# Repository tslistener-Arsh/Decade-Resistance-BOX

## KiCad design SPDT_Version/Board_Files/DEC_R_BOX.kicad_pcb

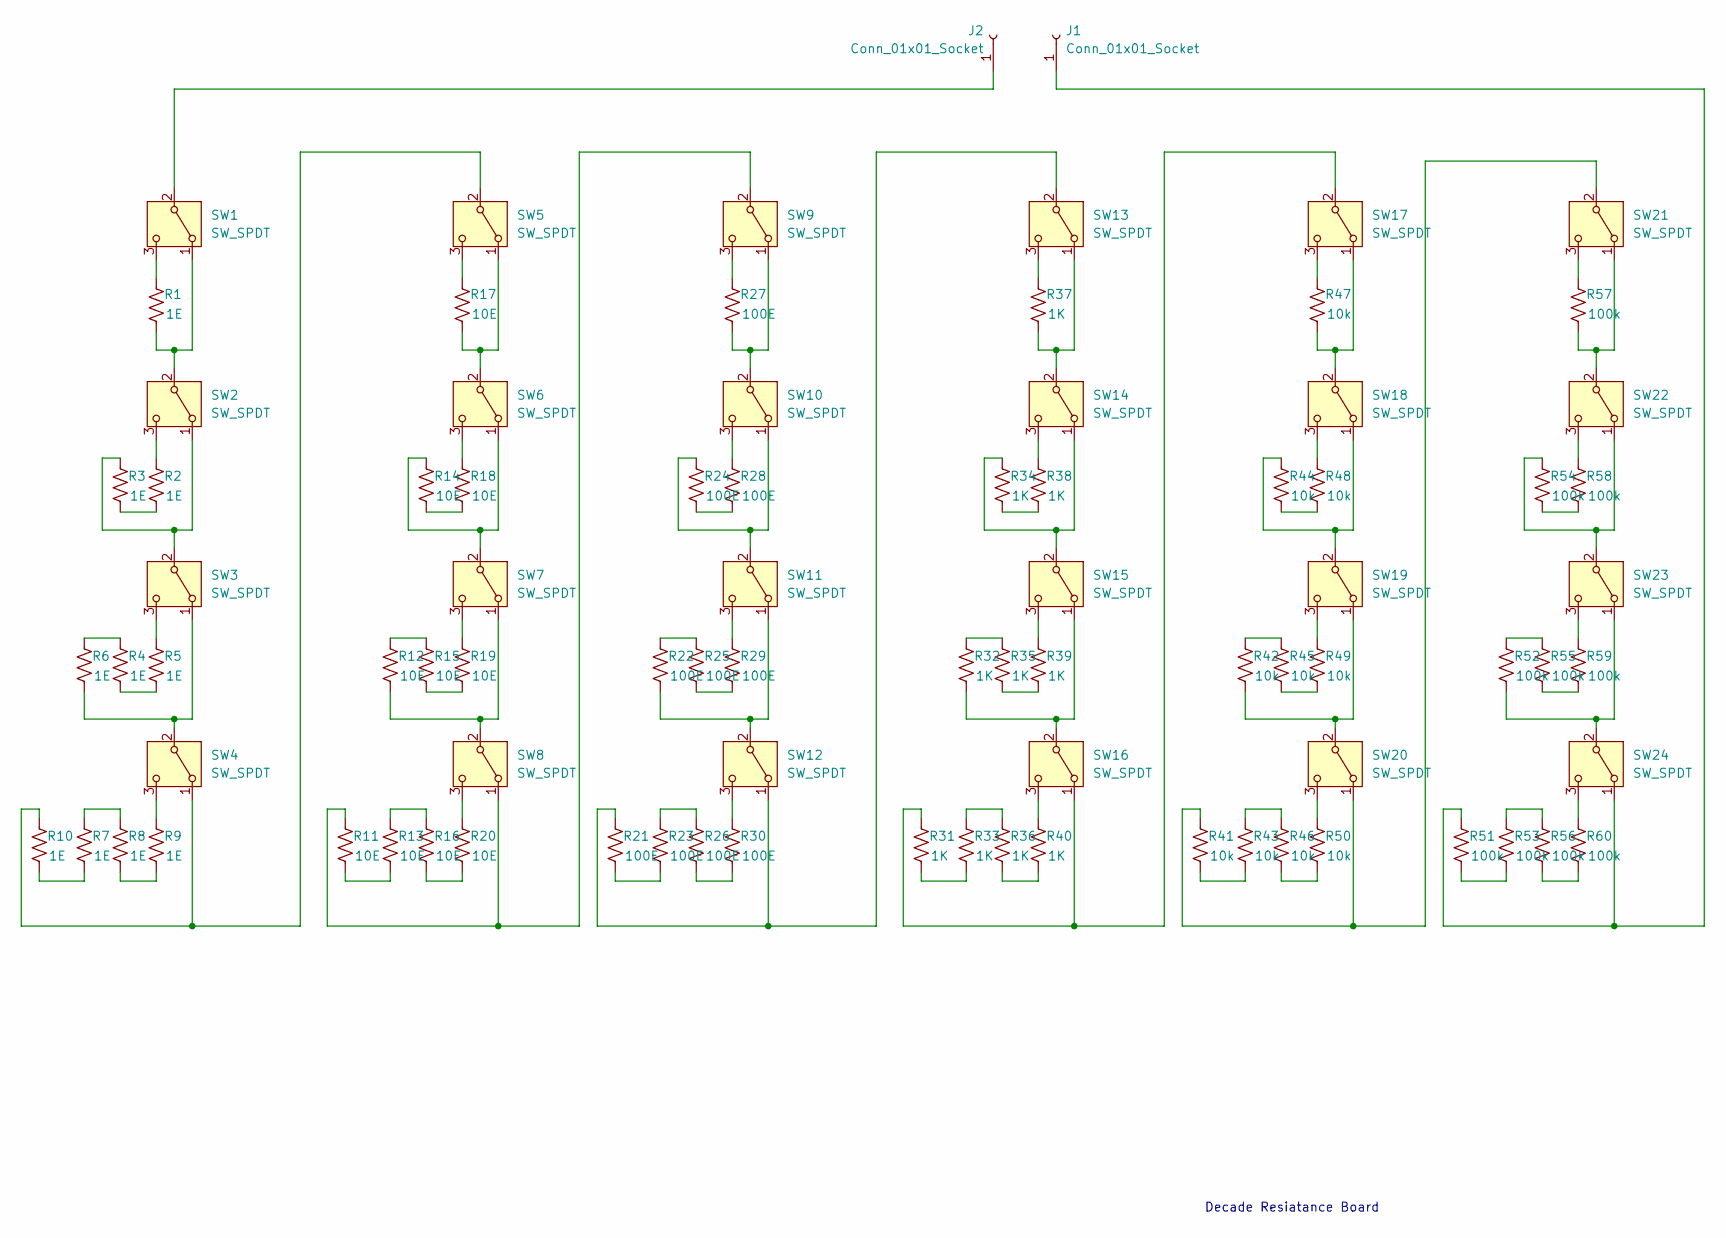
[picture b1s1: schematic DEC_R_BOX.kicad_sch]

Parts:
J1, J2: Conn_01x01_Socket; MountingHole_3.2mm_M3_DIN965_Pad
R1, R2, R3, R4, R5, R6, R7, R8, R9, R10: 1E; R_1206_3216Metric
R11, R12, R13, R14, R15, R16, R17, R18, R19, R20: 10E; R_1206_3216Metric
R21, R22, R23, R24, R25, R26, R27, R28, R29, R30: 100E; R_1206_3216Metric
R31, R32, R33, R34, R35, R36, R37, R38, R39, R40: 1K; R_1206_3216Metric
R41, R42, R43, R44, R45, R46, R47, R48, R49, R50: 10k; R_1206_3216Metric
R51, R52, R53, R54, R55, R56, R57, R58, R59, R60: 100k; R_1206_3216Metric
SW1, SW2, SW3, SW4, SW5, SW6, SW7, SW8, SW9, SW10, SW11, SW12, SW13, SW14, SW15, SW16, SW17, SW18, SW19, SW20, SW21, SW22, SW23, SW24: SW_SPDT; SIP3_11.6x8.5mm

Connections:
unnamed: J1.1, R51.1, SW24.1 (A)
unnamed: J2.1, SW1.2 (B)
unnamed: R2.2, R3.2
unnamed: R4.1, R6.1
unnamed: R4.2, R5.2
unnamed: R7.1, R8.1
unnamed: R8.2, R9.2
unnamed: R7.2, R10.2
unnamed: R11.2, R13.2
unnamed: R12.1, R15.1
unnamed: R13.1, R16.1
unnamed: R14.2, R18.2
unnamed: R15.2, R19.2
unnamed: R16.2, R20.2
unnamed: R21.2, R23.2
unnamed: R22.1, R25.1
unnamed: R23.1, R26.1
unnamed: R24.2, R28.2
unnamed: R25.2, R29.2
unnamed: R26.2, R30.2
unnamed: R31.2, R33.2
unnamed: R32.1, R35.1
unnamed: R33.1, R36.1
unnamed: R34.2, R38.2
unnamed: R35.2, R39.2
unnamed: R36.2, R40.2
unnamed: R41.2, R43.2
unnamed: R42.1, R45.1
unnamed: R43.1, R46.1
unnamed: R44.2, R48.2
unnamed: R45.2, R49.2
unnamed: R46.2, R50.2
unnamed: R51.2, R53.2
unnamed: R52.1, R55.1
unnamed: R53.1, R56.1
unnamed: R54.2, R58.2
unnamed: R55.2, R59.2
unnamed: R56.2, R60.2
unnamed: R1.2, SW1.1 (A), SW2.2 (B)
unnamed: R1.1, SW1.3 (C)
unnamed: R3.1, SW2.1 (A), SW3.2 (B)
unnamed: R2.1, SW2.3 (C)
unnamed: R6.2, SW3.1 (A), SW4.2 (B)
unnamed: R5.1, SW3.3 (C)
unnamed: R10.1, SW4.1 (A), SW5.2 (B)
unnamed: R9.1, SW4.3 (C)
unnamed: R17.2, SW5.1 (A), SW6.2 (B)
unnamed: R17.1, SW5.3 (C)
unnamed: R14.1, SW6.1 (A), SW7.2 (B)
unnamed: R18.1, SW6.3 (C)
unnamed: R12.2, SW7.1 (A), SW8.2 (B)
unnamed: R19.1, SW7.3 (C)
unnamed: R11.1, SW8.1 (A), SW9.2 (B)
unnamed: R20.1, SW8.3 (C)
unnamed: R27.1, SW9.3 (C)
unnamed: R24.1, SW10.1 (A), SW11.2 (B)
unnamed: R27.2, SW9.1 (A), SW10.2 (B)
unnamed: R28.1, SW10.3 (C)
unnamed: R22.2, SW11.1 (A), SW12.2 (B)
unnamed: R29.1, SW11.3 (C)
unnamed: R21.1, SW12.1 (A), SW13.2 (B)
unnamed: R30.1, SW12.3 (C)
unnamed: R37.2, SW13.1 (A), SW14.2 (B)
unnamed: R37.1, SW13.3 (C)
unnamed: R34.1, SW14.1 (A), SW15.2 (B)
unnamed: R38.1, SW14.3 (C)
unnamed: R32.2, SW15.1 (A), SW16.2 (B)
unnamed: R39.1, SW15.3 (C)
unnamed: R31.1, SW16.1 (A), SW17.2 (B)
unnamed: R40.1, SW16.3 (C)
unnamed: R47.2, SW17.1 (A), SW18.2 (B)
unnamed: R47.1, SW17.3 (C)
unnamed: R44.1, SW18.1 (A), SW19.2 (B)
unnamed: R48.1, SW18.3 (C)
unnamed: R42.2, SW19.1 (A), SW20.2 (B)
unnamed: R49.1, SW19.3 (C)
unnamed: R41.1, SW20.1 (A), SW21.2 (B)
unnamed: R50.1, SW20.3 (C)
unnamed: R57.2, SW21.1 (A), SW22.2 (B)
unnamed: R57.1, SW21.3 (C)
unnamed: R54.1, SW22.1 (A), SW23.2 (B)
unnamed: R58.1, SW22.3 (C)
unnamed: R52.2, SW23.1 (A), SW24.2 (B)
unnamed: R59.1, SW23.3 (C)
unnamed: R60.1, SW24.3 (C)

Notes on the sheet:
Decade Resiatance Board

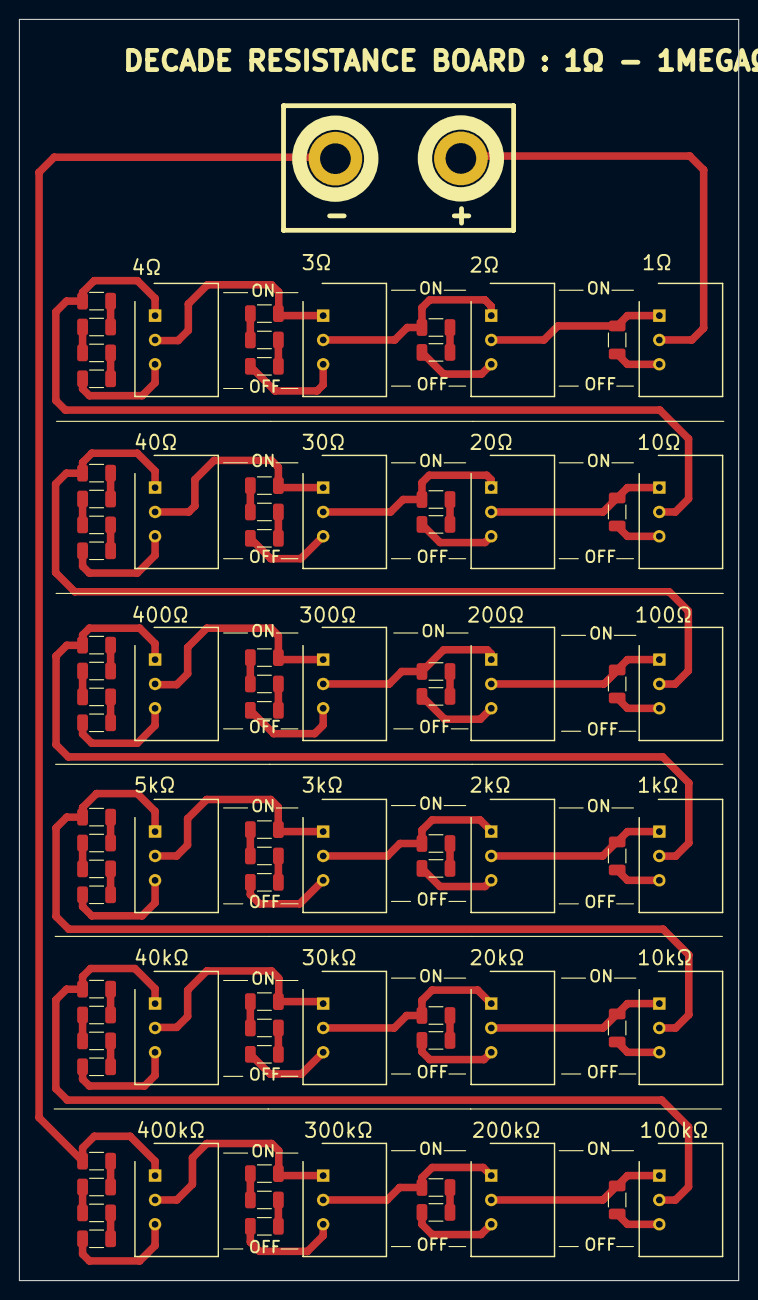
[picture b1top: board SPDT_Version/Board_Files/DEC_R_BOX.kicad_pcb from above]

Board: 2 copper layers, 75.0 x 131.6 mm, 86 parts (0 on the bottom side), 85 nets.

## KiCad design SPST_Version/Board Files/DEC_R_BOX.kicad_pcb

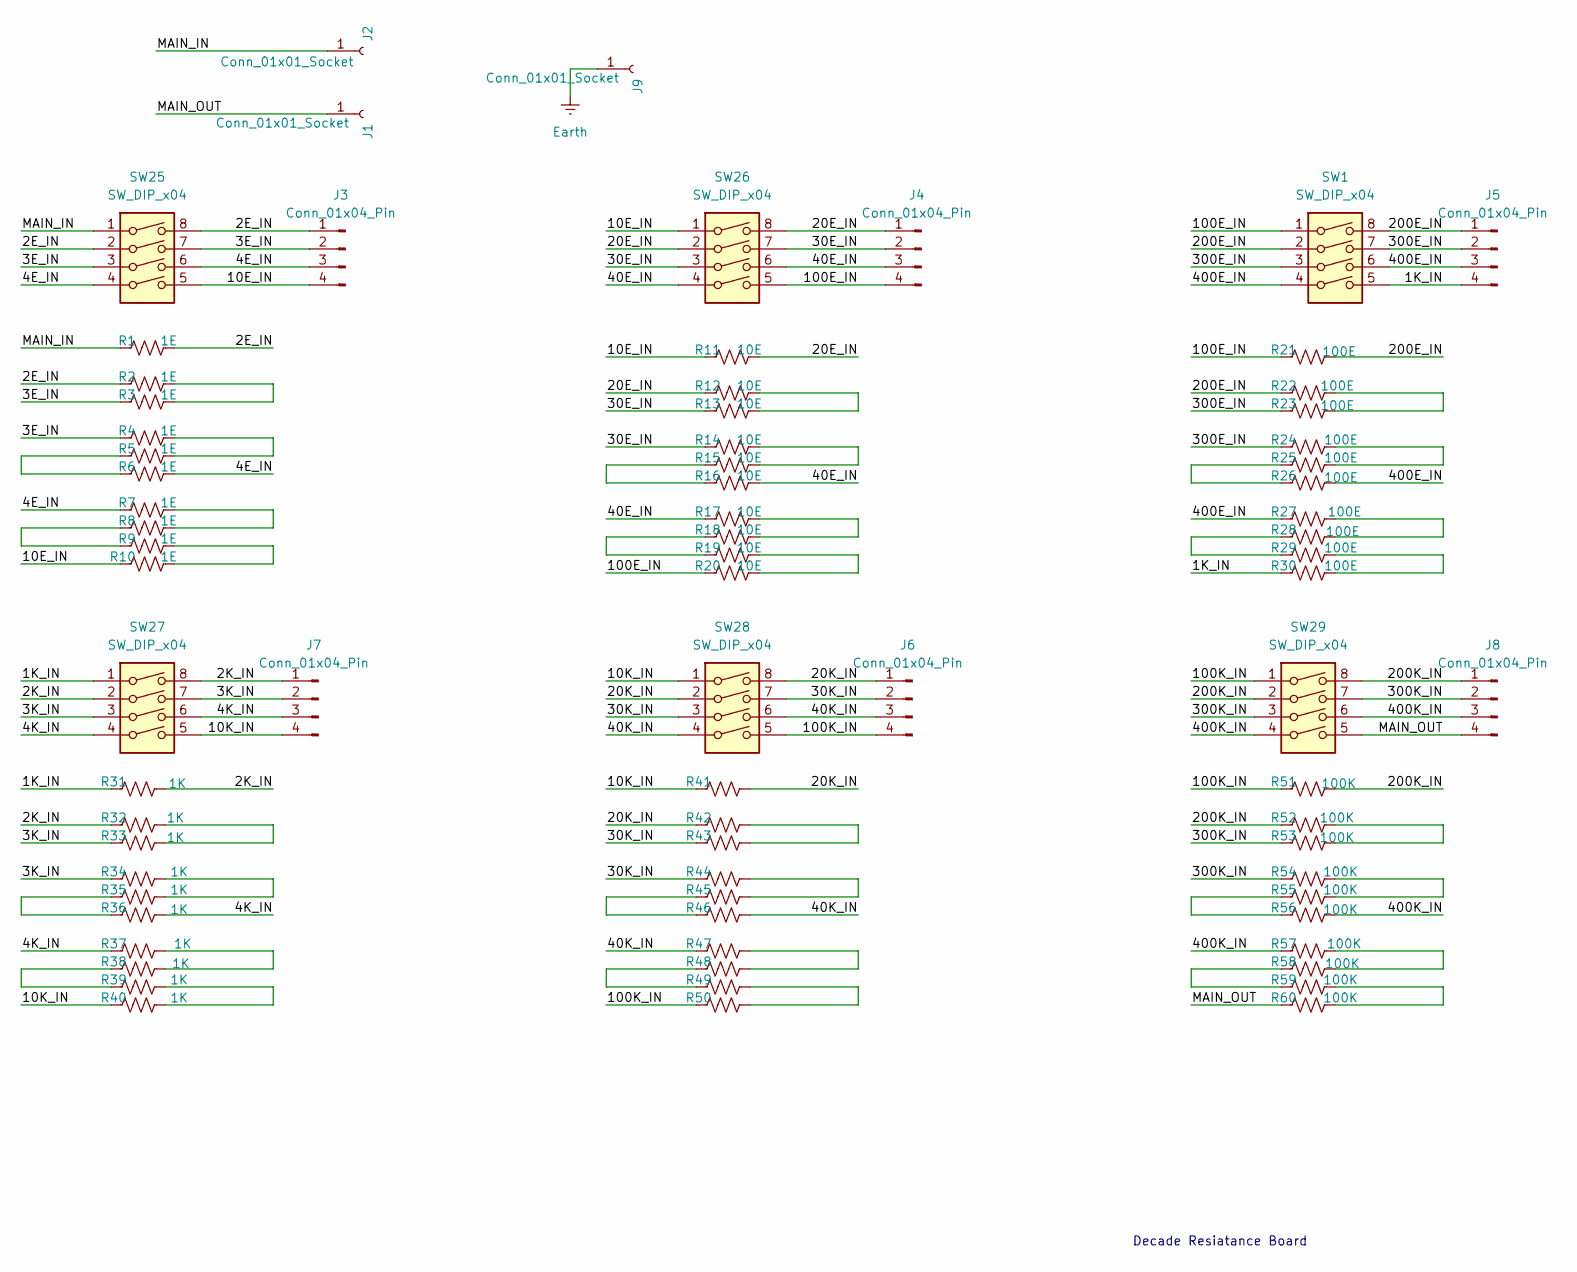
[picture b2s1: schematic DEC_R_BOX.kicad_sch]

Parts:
J1, J2, J9: Conn_01x01_Socket; MountingHole_3.2mm_M3_DIN965_Pad
J3, J4, J5, J6, J7, J8: Conn_01x04_Pin; PinHeader_1x04_P2.54mm_Vertical
R1, R2, R3, R4, R5, R6, R7, R8, R9, R10: 1E; R_1206_3216Metric
R11, R12, R13, R14, R15, R16, R17, R18, R19, R20: 10E; R_1206_3216Metric
R21, R22, R23, R24, R25, R26, R27, R28, R29, R30: 100E; R_1206_3216Metric
R31, R32, R33, R34, R35, R36, R37, R38, R39, R40: 1K; R_1206_3216Metric
R41, R42, R43, R44, R45, R46, R47, R48, R49, R50: 10K; R_1206_3216Metric
R51, R52, R53, R54, R55, R56, R57, R58, R59, R60: 100K; R_1206_3216Metric
SW1, SW25, SW26, SW27, SW28, SW29: SW_DIP_x04; DIP-8_Stripped

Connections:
/1K_IN: J5.4, R30.1, R31.1, SW1.5, SW27.1
/2E_IN: J3.1, R1.2, R2.1, SW25.2, SW25.8
/2K_IN: J7.1, R31.2, R32.1, SW27.2, SW27.8
/3E_IN: J3.2, R3.1, R4.1, SW25.3, SW25.7
/3K_IN: J7.2, R33.1, R34.1, SW27.3, SW27.7
/4E_IN: J3.3, R6.2, R7.1, SW25.4, SW25.6
/4K_IN: J7.3, R36.2, R37.1, SW27.4, SW27.6
/10E_IN: J3.4, R10.1, R11.1, SW25.5, SW26.1
/10K_IN: J7.4, R40.1, R41.1, SW27.5, SW28.1
/20E_IN: J4.1, R11.2, R12.1, SW26.2, SW26.8
/20K_IN: J6.1, R41.2, R42.1, SW28.2, SW28.8
/30E_IN: J4.2, R13.1, R14.1, SW26.3, SW26.7
/30K_IN: J6.2, R43.1, R44.1, SW28.3, SW28.7
/40E_IN: J4.3, R16.2, R17.1, SW26.4, SW26.6
/40K_IN: J6.3, R46.2, R47.1, SW28.4, SW28.6
/100E_IN: J4.4, R20.1, R21.1, SW1.1, SW26.5
/100K_IN: J6.4, R50.1, R51.1, SW28.5, SW29.1
/200E_IN: J5.1, R21.2, R22.1, SW1.2, SW1.8
/200K_IN: J8.1, R51.2, R52.1, SW29.2, SW29.8
/300E_IN: J5.2, R23.1, R24.1, SW1.3, SW1.7
/300K_IN: J8.2, R53.1, R54.1, SW29.3, SW29.7
/400E_IN: J5.3, R26.2, R27.1, SW1.4, SW1.6
/400K_IN: J8.3, R56.2, R57.1, SW29.4, SW29.6
/MAIN_IN: J2.1, R1.1, SW25.1
/MAIN_OUT: J1.1, J8.4, R60.1, SW29.5
Earth: J9.1
unnamed: R2.2, R3.2
unnamed: R4.2, R5.2
unnamed: R5.1, R6.1
unnamed: R7.2, R8.2
unnamed: R8.1, R9.1
unnamed: R9.2, R10.2
unnamed: R12.2, R13.2
unnamed: R14.2, R15.2
unnamed: R15.1, R16.1
unnamed: R17.2, R18.2
unnamed: R18.1, R19.1
unnamed: R19.2, R20.2
unnamed: R22.2, R23.2
unnamed: R24.2, R25.2
unnamed: R25.1, R26.1
unnamed: R27.2, R28.2
unnamed: R28.1, R29.1
unnamed: R29.2, R30.2
unnamed: R32.2, R33.2
unnamed: R34.2, R35.2
unnamed: R35.1, R36.1
unnamed: R37.2, R38.2
unnamed: R38.1, R39.1
unnamed: R39.2, R40.2
unnamed: R42.2, R43.2
unnamed: R44.2, R45.2
unnamed: R45.1, R46.1
unnamed: R47.2, R48.2
unnamed: R48.1, R49.1
unnamed: R49.2, R50.2
unnamed: R52.2, R53.2
unnamed: R54.2, R55.2
unnamed: R55.1, R56.1
unnamed: R57.2, R58.2
unnamed: R58.1, R59.1
unnamed: R59.2, R60.2

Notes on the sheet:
Decade Resiatance Board

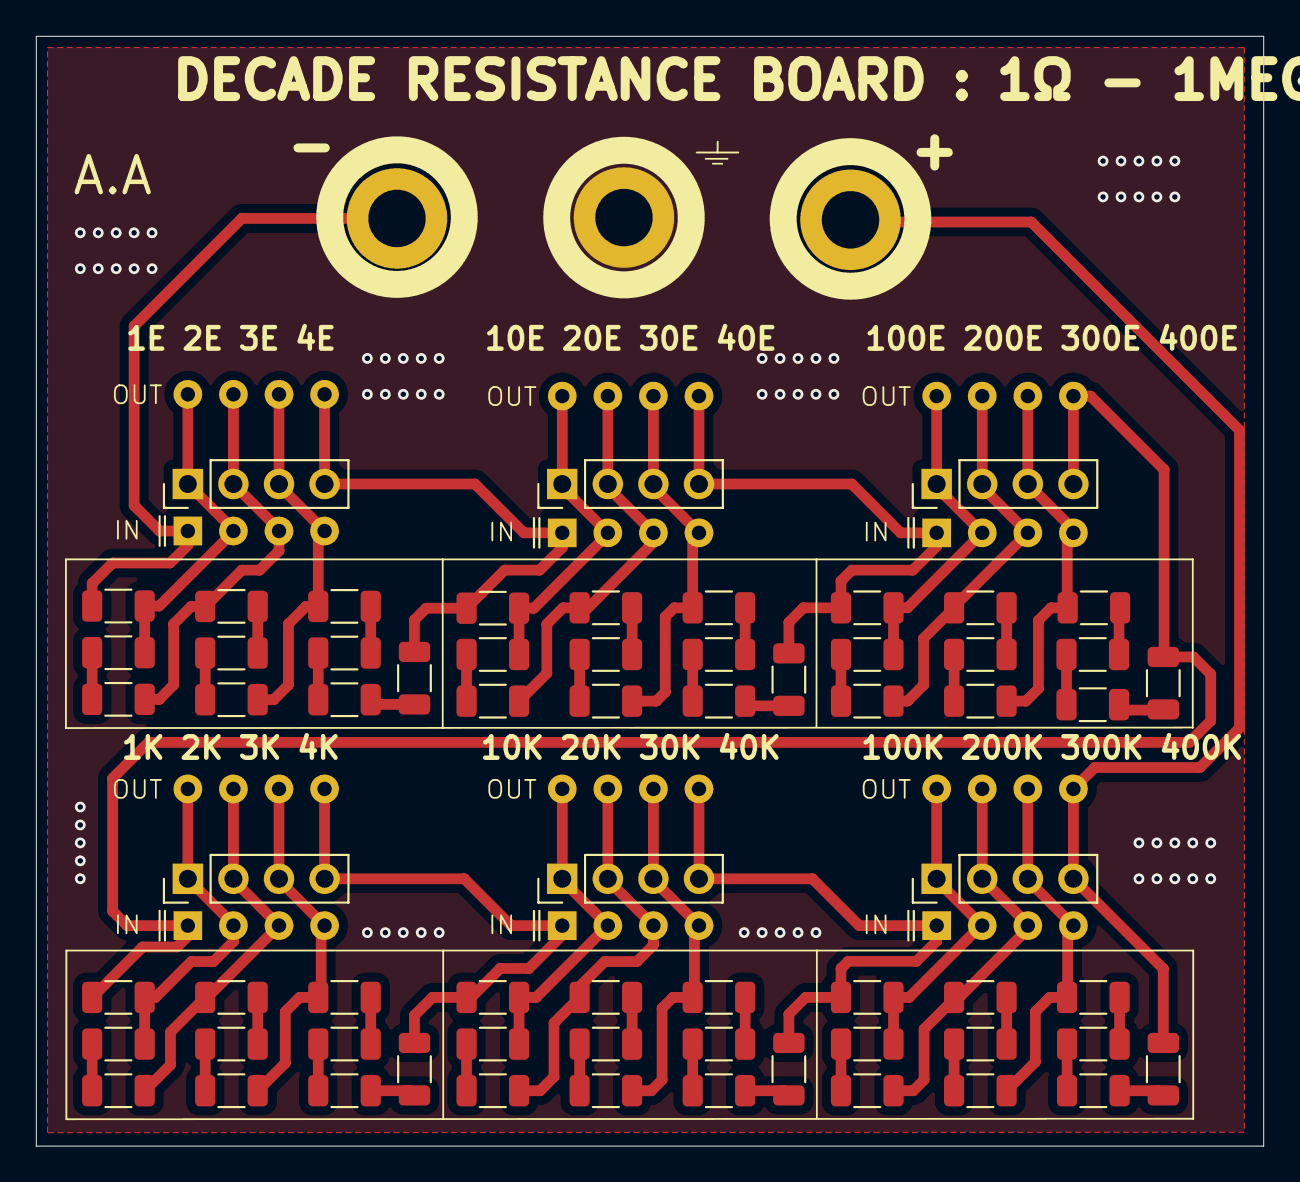
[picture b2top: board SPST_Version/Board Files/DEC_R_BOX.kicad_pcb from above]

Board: 2 copper layers, 68.4 x 61.9 mm, 75 parts (0 on the bottom side), 61 nets.

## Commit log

2024-08-17 Iniital Commit
2024-08-20 Added one smaller SPST version that use DIP swicthes/Pin headers
